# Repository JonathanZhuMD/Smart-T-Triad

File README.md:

# Smart-T-Triad
Scalable IR Touch Interface

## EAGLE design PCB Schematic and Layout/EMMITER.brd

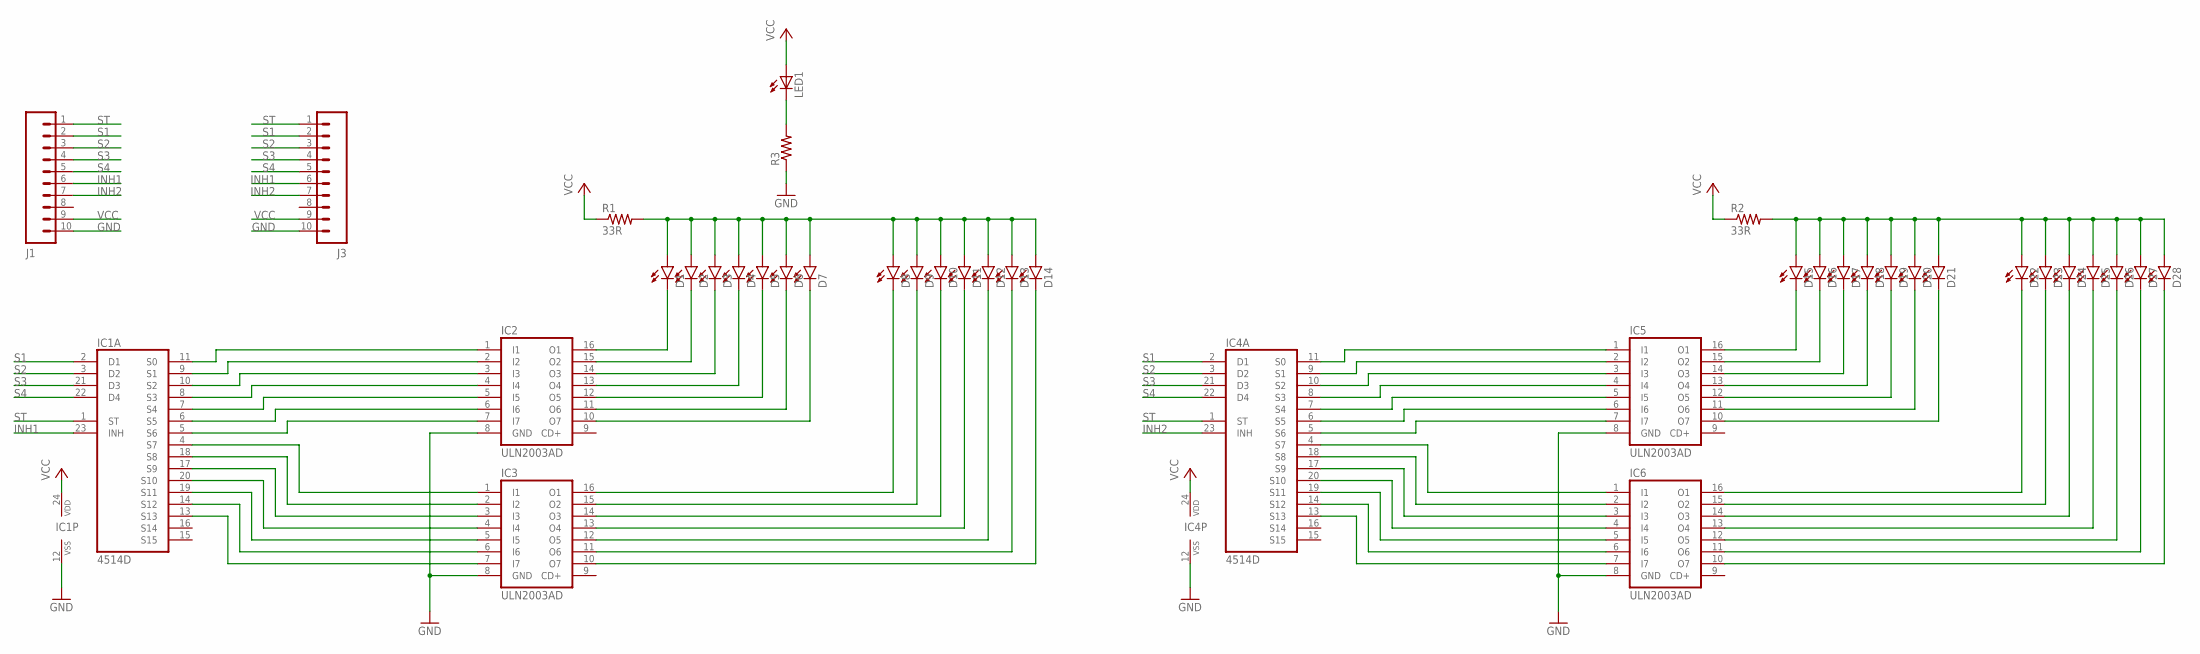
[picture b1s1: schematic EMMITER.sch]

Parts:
D1, D2, D3, D4, D5, D6, D7, D8, D9, D10, D11, D12, D13, D14, D15, D16, D17, D18, D19, D20, D21, D22, D23, D24, D25, D26, D27, D28: LED5MM
IC1, IC4: 4514D; SO24W
IC2, IC3, IC5, IC6: ULN2003AD; SO16
J1, J3: M10LOCK; 1X10_LOCK
LED1: LEDSMT1206; 1206
R1, R2: 33R; AXIAL-0.8
R3: R-US_M1206; M1206

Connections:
GND: IC1.12 (VSS), IC2.8 (GND), IC3.8 (GND), IC4.12 (VSS), IC5.8 (GND), IC6.8 (GND), J1.10, J3.10, R3.1
INH1: IC1.23 (INH), J1.6, J3.6
INH2: IC4.23 (INH), J1.7, J3.7
unnamed: IC1.11 (S0), IC2.1 (I1)
unnamed: IC1.9 (S1), IC2.2 (I2)
unnamed: IC1.10 (S2), IC2.3 (I3)
unnamed: IC1.8 (S3), IC2.4 (I4)
unnamed: IC1.7 (S4), IC2.5 (I5)
unnamed: IC1.6 (S5), IC2.6 (I6)
unnamed: IC1.5 (S6), IC2.7 (I7)
unnamed: IC1.4 (S7), IC3.1 (I1)
unnamed: IC1.18 (S8), IC3.2 (I2)
unnamed: IC1.17 (S9), IC3.3 (I3)
unnamed: IC1.20 (S10), IC3.4 (I4)
unnamed: IC1.19 (S11), IC3.5 (I5)
unnamed: IC1.14 (S12), IC3.6 (I6)
unnamed: IC1.13 (S13), IC3.7 (I7)
unnamed: D1.K (C), IC2.16 (O1)
unnamed: D2.K (C), IC2.15 (O2)
unnamed: D3.K (C), IC2.14 (O3)
unnamed: D4.K (C), IC2.13 (O4)
unnamed: D5.K (C), IC2.12 (O5)
unnamed: D6.K (C), IC2.11 (O6)
unnamed: D7.K (C), IC2.10 (O7)
unnamed: D8.K (C), IC3.16 (O1)
unnamed: D9.K (C), IC3.15 (O2)
unnamed: D10.K (C), IC3.14 (O3)
unnamed: D11.K (C), IC3.13 (O4)
unnamed: D12.K (C), IC3.12 (O5)
unnamed: D13.K (C), IC3.11 (O6)
unnamed: D14.K (C), IC3.10 (O7)
unnamed: IC4.11 (S0), IC5.1 (I1)
unnamed: D1.A, D2.A, D3.A, D4.A, D5.A, D6.A, D7.A, D8.A, D9.A, D10.A, D11.A, D12.A, D13.A, D14.A, R1.P$2 (2)
unnamed: IC4.9 (S1), IC5.2 (I2)
unnamed: IC4.10 (S2), IC5.3 (I3)
unnamed: IC4.8 (S3), IC5.4 (I4)
unnamed: IC4.7 (S4), IC5.5 (I5)
unnamed: IC4.6 (S5), IC5.6 (I6)
unnamed: IC4.5 (S6), IC5.7 (I7)
unnamed: IC4.4 (S7), IC6.1 (I1)
unnamed: IC4.18 (S8), IC6.2 (I2)
unnamed: IC4.17 (S9), IC6.3 (I3)
unnamed: IC4.20 (S10), IC6.4 (I4)
unnamed: IC4.19 (S11), IC6.5 (I5)
unnamed: IC4.14 (S12), IC6.6 (I6)
unnamed: IC4.13 (S13), IC6.7 (I7)
unnamed: D15.K (C), IC5.16 (O1)
unnamed: D16.K (C), IC5.15 (O2)
unnamed: D17.K (C), IC5.14 (O3)
unnamed: D18.K (C), IC5.13 (O4)
unnamed: D19.K (C), IC5.12 (O5)
unnamed: D20.K (C), IC5.11 (O6)
unnamed: D21.K (C), IC5.10 (O7)
unnamed: D22.K (C), IC6.16 (O1)
unnamed: D23.K (C), IC6.15 (O2)
unnamed: D24.K (C), IC6.14 (O3)
unnamed: D25.K (C), IC6.13 (O4)
unnamed: D26.K (C), IC6.12 (O5)
unnamed: D27.K (C), IC6.11 (O6)
unnamed: D28.K (C), IC6.10 (O7)
unnamed: D15.A, D16.A, D17.A, D18.A, D19.A, D20.A, D21.A, D22.A, D23.A, D24.A, D25.A, D26.A, D27.A, D28.A, R2.P$2 (2)
unnamed: LED1.C, R3.2
S1: IC1.2 (D1), IC4.2 (D1), J1.2, J3.2
S2: IC1.3 (D2), IC4.3 (D2), J1.3, J3.3
S3: IC1.21 (D3), IC4.21 (D3), J1.4, J3.4
S4: IC1.22 (D4), IC4.22 (D4), J1.5, J3.5
ST: IC1.1 (ST), IC4.1 (ST), J1.1, J3.1
VCC: IC1.24 (VDD), IC4.24 (VDD), J1.9, J3.9, LED1.A, R1.P$1 (1), R2.P$1 (1)

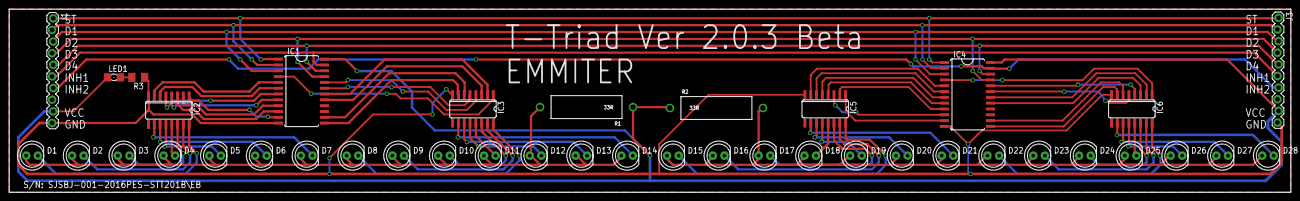
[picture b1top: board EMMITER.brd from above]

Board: 2 copper layers, 280.0 x 40.0 mm, 40 parts (0 on the bottom side), 68 nets.

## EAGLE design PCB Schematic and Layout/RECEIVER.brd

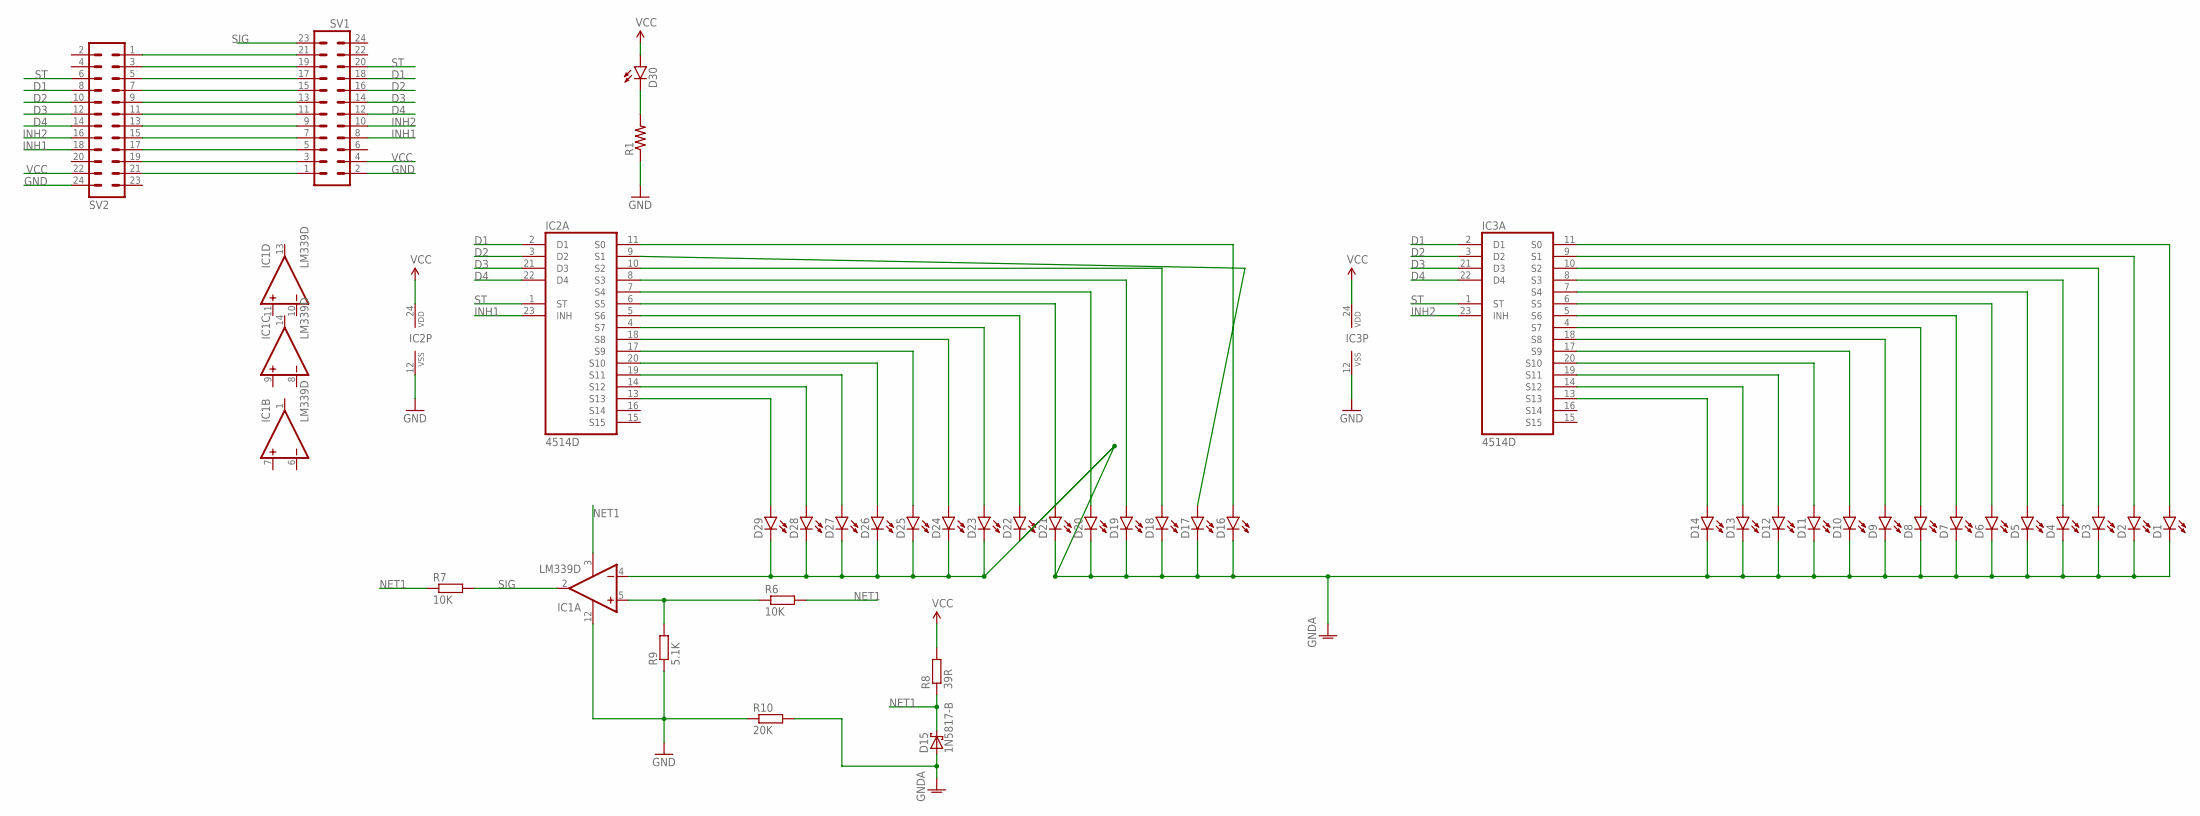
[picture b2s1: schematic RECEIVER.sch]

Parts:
D1, D2, D3, D4, D5, D6, D7, D8, D9, D10, D11, D12, D13, D14, D16, D17, D18, D19, D20, D21, D22, D23, D24, D25, D26, D27, D28, D29: LED5MM
D15: 1N5817-B; DO41-7.6
D30: LED1206; LED-1206
IC1: LM339D; SO14
IC2, IC3: 4514D; SO24W
R1: RESISTOR1206; 1206
R6, R7: 10K; 0207/10
R8: 39R; 0207/10
R9: 5.1K; 0207/10
R10: 20K; 0207/10
SV1, SV2: MA12-2W

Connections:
D1: IC2.2 (D1), IC3.2 (D1), SV1.18, SV2.8
D2: IC2.3 (D2), IC3.3 (D2), SV1.16, SV2.10
D3: IC2.21 (D3), IC3.21 (D3), SV1.14, SV2.12
D4: IC2.22 (D4), IC3.22 (D4), SV1.12, SV2.14
GND: IC1.12 (GND), IC2.12 (VSS), IC3.12 (VSS), R1.1, R9.1, R10.1, SV1.2, SV2.24
GNDA: D1.K (C), D2.K (C), D3.K (C), D4.K (C), D5.K (C), D6.K (C), D7.K (C), D8.K (C), D9.K (C), D10.K (C), D11.K (C), D12.K (C), D13.K (C), D14.K (C), D15.A, D16.K (C), D17.K (C), D18.K (C), D19.K (C), D20.K (C), D21.K (C), D22.K (C), D23.K (C), D24.K (C), D25.K (C), D26.K (C), D27.K (C), D28.K (C), D29.K (C), IC1.4 (-IN), R10.2
INH1: IC2.23 (INH), SV1.8, SV2.18
INH2: IC3.23 (INH), SV1.10, SV2.16
unnamed: D16.A, IC2.11 (S0)
unnamed: D17.A, IC2.9 (S1)
unnamed: D18.A, IC2.10 (S2)
unnamed: D19.A, IC2.8 (S3)
unnamed: D20.A, IC2.7 (S4)
unnamed: D21.A, IC2.6 (S5)
unnamed: D22.A, IC2.5 (S6)
unnamed: D23.A, IC2.4 (S7)
unnamed: D24.A, IC2.18 (S8)
unnamed: D25.A, IC2.17 (S9)
unnamed: D26.A, IC2.20 (S10)
unnamed: D27.A, IC2.19 (S11)
unnamed: D28.A, IC2.14 (S12)
unnamed: D29.A, IC2.13 (S13)
unnamed: SV1.7, SV2.15
unnamed: IC1.5 (+IN), R6.1, R9.2
unnamed: SV1.21, SV2.1
unnamed: SV1.19, SV2.3
unnamed: SV1.17, SV2.5
unnamed: SV1.15, SV2.7
unnamed: SV1.13, SV2.9
unnamed: SV1.11, SV2.11
unnamed: SV1.9, SV2.13
unnamed: D1.A, IC3.11 (S0)
unnamed: D2.A, IC3.9 (S1)
unnamed: D3.A, IC3.10 (S2)
unnamed: D4.A, IC3.8 (S3)
unnamed: D5.A, IC3.7 (S4)
unnamed: D6.A, IC3.6 (S5)
unnamed: D7.A, IC3.5 (S6)
unnamed: D8.A, IC3.4 (S7)
unnamed: D9.A, IC3.18 (S8)
unnamed: D10.A, IC3.17 (S9)
unnamed: D11.A, IC3.20 (S10)
unnamed: D12.A, IC3.19 (S11)
unnamed: D13.A, IC3.14 (S12)
unnamed: D14.A, IC3.13 (S13)
unnamed: SV1.5, SV2.17
unnamed: SV1.3, SV2.19
unnamed: SV1.1, SV2.21
unnamed: D30.C, R1.2
NET1: D15.C, IC1.3 (V+), R6.2, R7.1, R8.1
SIG: IC1.2 (OUT), R7.2, SV1.23
ST: IC2.1 (ST), IC3.1 (ST), SV1.20, SV2.6
VCC: D30.A, IC2.24 (VDD), IC3.24 (VDD), R8.2, SV1.4, SV2.22

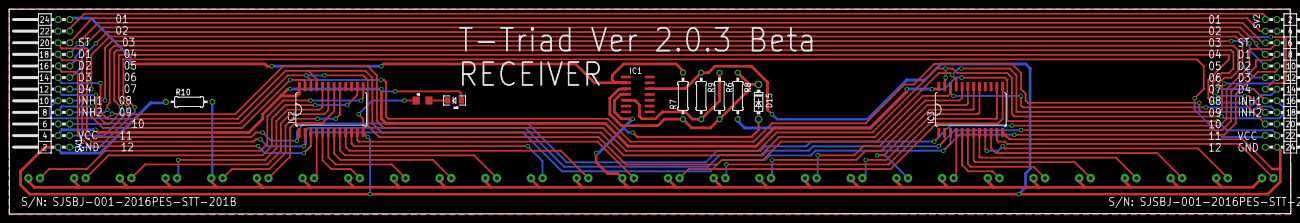
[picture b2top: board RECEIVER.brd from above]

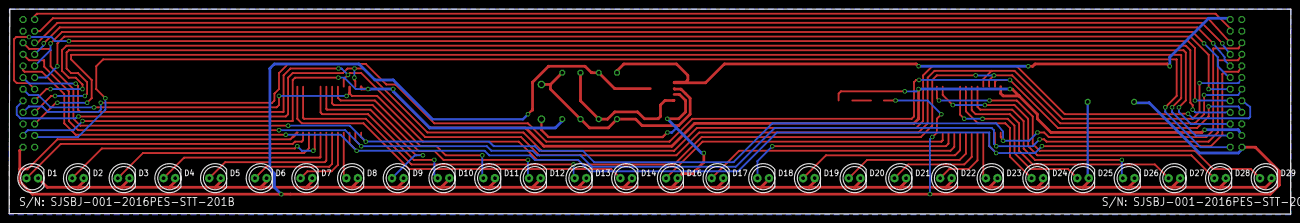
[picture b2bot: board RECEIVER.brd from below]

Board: 2 copper layers, 280.6 x 44.9 mm, 41 parts (28 on the bottom side), 53 nets.

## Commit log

2016-12-31 Initialization

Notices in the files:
parts and their libraries:
SparkFun-LED: Licensing: Creative Commons ShareAlike 4.0 International - https://creativecommons.org/licenses/by-sa/4.0
